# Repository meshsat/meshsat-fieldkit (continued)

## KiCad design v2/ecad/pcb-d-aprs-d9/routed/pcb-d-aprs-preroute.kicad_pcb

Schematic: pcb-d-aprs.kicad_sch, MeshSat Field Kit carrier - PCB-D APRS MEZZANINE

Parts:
C1, C2, C5: 47u 6.3V X5R 1210; C_1210_3225Metric
C3, C9, C17, C24, C25, C33, C40: 10u; C_0805_2012Metric
C4, C6, C11, C15, C16, C39, C49, C50, C51, C52, C53, C54, C55, C56, C57, C62, C63: 100n; C_0603_1608Metric
C7, C8, C12, C18, C19, C20, C21, C22, C23, C28, C29, C30, C31, C32, C34, C35, C36, C37, C38, C41, C42, C46, C47, C48: 1u; C_0603_1608Metric
C10: 4.7u; C_0805_2012Metric
C13, C14: 27p NP0; C_0402_1005Metric
C26, C27: 18p NP0; C_0402_1005Metric
C43: 100p NP0; C_0402_1005Metric
C44, C45: 1n NP0; C_0402_1005Metric
C58, C60: 22p 500V NP0 1206; C_1206_3216Metric
C59: 39p 500V NP0 1206; C_1206_3216Metric
C61: 4.7n; C_0402_1005Metric
D1: SMBJ5.0A; D_SMB
D2: 1N4148W coil flyback; D_SOD-123
FB1: 600R 2A ferrite (the exciter's 1 A transmit pulse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; L_0805_2012Metric
JP1: electret bias headset 1 (close for an electret mi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; SolderJumper-2_P1.3mm_Open_RoundedPad1.0x1.5mm
JP2: electret bias headset 2; SolderJumper-2_P1.3mm_Open_RoundedPad1.0x1.5mm
J_ANT: SMA jack: antenna pigtail to A22's VHF jack J_RF1; SMA_Amphenol_132134_Vertical; LCSC C3174425
J_HARN1: A22 mezzanine harness J_MEZZ1 (IDC 2x8): USB pair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; IDC-Header_2x08_P2.54mm_Vertical_NarrowPad
J_HS1: JST-PH 1x5 socket: headset 1, SPK GND MIC GND PTT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; JST_PH_B5B-PH-K_1x05_P2.00mm_Vertical; LCSC C157993
J_HS2: JST-PH 1x5 socket: headset 2, SPK GND MIC GND PTT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; JST_PH_B5B-PH-K_1x05_P2.00mm_Vertical; LCSC C157993
J_PAIN: U.FL socket: PA drive (coax to the RA30H1317M1 in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; U.FL_Hirose_U.FL-R-SMT-1_Vertical; LCSC C88373
J_PAOUT: SMA jack: PA output (coax from the RA30H1317M1 ou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; SMA_Amphenol_132134_Vertical; LCSC C3174425
J_PWR1: JST-VH socket, 10 A: 5 V from A22 J_MEZZ_PWR1 (be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; JST_VH_B2P-VH_1x02_P3.96mm_Vertical; LCSC C274411
J_USB3: JST-PH 1x4 socket: spare hub port 3, 5V D- D+ GND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; JST_PH_B4B-PH-K_1x04_P2.00mm_Vertical; LCSC C131334
J_VGG: JST-PH 1x2 socket: PA gate bias, VGG GND (the lea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; JST_PH_B2B-PH-K_1x02_P2.00mm_Vertical; LCSC C5251182
K1: Omron G6K-2F-Y 5 VDC DPDT signal relay, T/R; Relay_DPDT_Omron_G6K-2F-Y
L1: 68nH 0805 (LPF, 145 MHz 5th order; values to be v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; L_0805_2012Metric
L2: 68nH 0805 (LPF); L_0805_2012Metric
LED1: green power; LED_0603_1608Metric; LCSC C12624
LED2: amber record; LED_0603_1608Metric; LCSC C2287
LED3: green playback; LED_0603_1608Metric; LCSC C12624
LED4: red transmit; LED_0603_1608Metric; LCSC C2286
LED5: amber PA keyed; LED_0603_1608Metric; LCSC C2287
LED6: green receive (AUDIO_ON low); LED_0603_1608Metric; LCSC C12624
Q1: 2N7002 PA_EN -> H/L low (never tie H/L high); SOT-23; LCSC C8545
Q2: 2N7002 relay coil; SOT-23; LCSC C8545
Q3, Q4, Q5, Q6, Q7, Q8, Q9: 2N7002; SOT-23; LCSC C8545
R1, R43, R44, R51: 2.2k; R_0603_1608Metric
R2, R3, R34, R53: 100k; R_0603_1608Metric
R4, R29, R30, R49, R50, R52: 1k; R_0603_1608Metric
R5, R9, R10, R31, R32, R35, R36, R37, R38, R39, R45, R46, R47, R66, R67, R68, R69, R70, R71, R72, R73, R74, R75, R76, R77, R78, R79: 10k; R_0603_1608Metric
R6, R7, R12, R13, R16, R17, R20, R21: 22; R_0603_1608Metric
R8, R11, R28: 1.5k; R_0603_1608Metric
R14, R15, R18, R19, R22, R23, R24, R25: 15k; R_0603_1608Metric
R26, R27: 33; R_0603_1608Metric
R33, R40, R41: 4.7k; R_0603_1608Metric
R42: 220k; R_0603_1608Metric
R48: 100; R_0603_1608Metric
R54, R56: 27 1% 2010; R_2010_5025Metric
R55: 36 1% 2010; R_2010_5025Metric
TP1: AF_OUT; TestPoint_Pad_D1.5mm
TP2: MIC_SUM; TestPoint_Pad_D1.5mm
TP3: KEY; TestPoint_Pad_D1.5mm
TP4: PA_KEY; TestPoint_Pad_D1.5mm
TP5: +3V3_D8; TestPoint_Pad_D1.5mm
TP6: +5V_D8; TestPoint_Pad_D1.5mm
TP7: VGG_SW; TestPoint_Pad_D1.5mm
TP8: RX_MIX; TestPoint_Pad_D1.5mm
TP9: ZEROIZE_HW; TestPoint_Pad_D1.5mm
TP10: AB_SPARE; TestPoint_Pad_D1.5mm
TP11: SA_TXD; TestPoint_Pad_D1.5mm
TP12: SA_RXD; TestPoint_Pad_D1.5mm
TP13: PTT_SW_n; TestPoint_Pad_D1.5mm
TP14: SA_PD; TestPoint_Pad_D1.5mm
TP15: TX_INHIBIT_n; TestPoint_Pad_D1.5mm
TP16: PA_EN; TestPoint_Pad_D1.5mm
TP17: EXP_SPARE1; TestPoint_Pad_D1.5mm
TP18: EXP_SPARE2; TestPoint_Pad_D1.5mm
TP19: EXP_SPARE3; TestPoint_Pad_D1.5mm
TP20: EXP_SPARE4; TestPoint_Pad_D1.5mm
TP21: EXP_SPARE5; TestPoint_Pad_D1.5mm
TP22: EXP_SPARE6; TestPoint_Pad_D1.5mm
TP23: EXP_SPARE7; TestPoint_Pad_D1.5mm
TP24: EXP_SPARE8; TestPoint_Pad_D1.5mm
U1: TLV75533PDBV 3.3 V 500 mA LDO (1 IN 2 GND 3 EN 4 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; SOT-23-5
U2: NiceRF SA868 VHF 2 W exciter, bench-fitted (caste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; NiceRF_SA868
U3: CP2102N-A02-GQFN28 USB-UART bridge (SAU); QFN-28-1EP_5x5mm_P0.5mm_EP3.35x3.35mm; LCSC C964632
U4: TUSB2046BI four-port USB 2.0 full-speed hub (LQFP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; LQFP-32_7x7mm_P0.8mm
U5: USBLC6-2SC6; SOT-23-6; LCSC C7519
U6: TI PCM2912A USB audio codec (TQFP-32): mono input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; TQFP-32_7x7mm_P0.8mm
U7: TI TPA6132A2 headphone amplifier (QFN-16), receiv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; QFN-16-1EP_3x3mm_P0.5mm_EP1.75x1.75mm
U8: TLV9062IDGK dual op amp (1 OUT1 2 IN1- 3 IN1+ 4 V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; VSSOP-8_3x3mm_P0.65mm
U9: 74LVC1G08 AND (1 A 2 B 3 GND 4 Y 5 VCC): both hea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; SOT-23-5
U10: 74LVC1G08 AND: headsets AND software PTT (RTS); SOT-23-5
U11: 74LVC1G04 inverter (2 A 4 Y): PTT_ANY; SOT-23-5
U12: 74LVC1G08 AND: KEY = PTT_ANY AND TX_INHIBIT_n (th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; SOT-23-5
U13: 74LVC1G04 inverter: KEY -> SA868 PTT (low = trans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; SOT-23-5
U14: 74LVC1G08 AND: PA_KEY = KEY AND PA_EN (A22's PA r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; SOT-23-5
U15: TPS22810DRV; WSON-6-1EP_2x2mm_P0.65mm_EP1x1.6mm
U16: PCA9555PW 0x26: COS, PTT states, KEY, PA_KEY in; 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; TSSOP-24_4.4x7.8mm_P0.65mm
Y1: 6 MHz 3225 (CL 20 pF; C1 = C2 = 27 pF and Rd 1.5k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; Crystal_SMD_3225-4Pin_3.2x2.5mm
Y2: 6 MHz 3225 (codec clock; 18 pF loads, to confirm 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; Crystal_SMD_3225-4Pin_3.2x2.5mm

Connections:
/+3V3: C63.1, J_HARN1.13, R67.2, R69.2, R71.2, R73.2, R75.2, R77.2, R79.2, U16.2 (A1), U16.3 (A2), U16.24 (VDD)
/+3V3_D8: C8.1, C9.1, C15.1, C16.1, C17.1, C51.1, C52.1, C53.1, C54.1, C55.1, C56.1, Q3.1 (G), Q4.1 (G), Q5.1 (G), Q6.1 (G), Q7.1 (G), Q8.1 (G), Q9.1 (G), R1.1, R5.2, R8.2, R9.2, R10.2, R29.1, R30.1, R51.1, R66.2, R68.2, R70.2, R72.2, R74.2, R76.2, R78.2, TP5.1, U1.5 (+3V3_D8), U4.3 (VCC), U4.6 (EEDATA/GANGED), U4.25 (VCC), U4.26 (EXTMEM), U7.6 (G0), U9.5 (+3V3_D8), U10.5 (+3V3_D8), U11.5 (+3V3_D8), U12.5 (+3V3_D8), U13.5 (+3V3_D8), U14.5 (+3V3_D8)
/+5V_D8: C1.1, C2.1, C3.1, C4.1, C7.1, C18.1, C32.1, C33.1, C39.1, C57.1, D1.2 (A2), D2.1 (K), FB1.1, J_PWR1.1, J_USB3.1, K1.1, R38.1, R43.2, R44.2, TP6.1, U1.1 (+5V_D8), U1.3 (+5V_D8), U3.7 (VREGIN), U3.8 (VBUS), U5.5 (VBUS), U6.2 (VBUS), U7.14 (VDD), U8.8 (+5V_D8), U15.6 (VIN)
/+5V_SA: C5.1, C6.1, FB1.2, U2.8 (VBAT)
/AB_SPARE: J_HARN1.16, TP10.1
/AF_DIV: C28.1, R31.2, R32.1
/AF_OUT: R31.1, R35.1, TP1.1, U2.3 (AF_OUT)
/AMP_CPN: C30.2, U7.9 (CPN)
/AMP_CPP: C30.1, U7.11 (CPP)
/AMP_EN: Q9.2 (S), R78.1, U7.13 (EN)
/AMP_HPVDD: C31.1, U7.12 (HPVDD)
/AMP_HPVSS: C29.1, U7.8 (HPVSS)
/AMP_INL_N: C37.1, U7.1 (INL-)
/AMP_INL_P: C35.2, U7.2 (INL+)
/AMP_INR_N: C38.1, U7.4 (INR-)
/AMP_INR_P: C36.2, U7.3 (INR+)
/EXP_INT: J_HARN1.12, U16.1 (~INT)
/EXP_SPARE1: TP17.1, U16.13 (IO1_0)
/EXP_SPARE2: TP18.1, U16.14 (IO1_1)
/EXP_SPARE3: TP19.1, U16.15 (IO1_2)
/EXP_SPARE4: TP20.1, U16.16 (IO1_3)
/EXP_SPARE5: TP21.1, U16.17 (IO1_4)
/EXP_SPARE6: TP22.1, U16.18 (IO1_5)
/EXP_SPARE7: TP23.1, U16.19 (IO1_6)
/EXP_SPARE8: TP24.1, U16.20 (IO1_7)
/HS1_BIAS_R: JP1.2 (B), R43.1
/HS1_MIC: C41.1, C44.1, JP1.1 (A), J_HS1.3
/HS1_MIC_AC: C41.2, R40.1
/HS1_SPK: J_HS1.1, U7.16 (OUTL)
/HS2_BIAS_R: JP2.2 (B), R44.1
/HS2_MIC: C42.1, C45.1, JP2.1 (A), J_HS2.3
/HS2_MIC_AC: C42.2, R41.1
/HS2_SPK: J_HS2.1, U7.5 (OUTR)
/HUB_DM0: R7.2, U4.2 (DM0)
/HUB_DM1: R13.1, U4.11 (DM1)
/HUB_DM2: R17.1, U4.15 (DM2)
/HUB_DM3: R21.1, U4.19 (DM3)
/HUB_DM4: R25.1, U4.23 (DM4)
/HUB_DP0: R6.2, R8.1, U4.1 (DP0)
/HUB_DP1: R12.1, U4.12 (DP1)
/HUB_DP2: R16.1, U4.16 (DP2)
/HUB_DP3: R20.1, U4.20 (DP3)
/HUB_DP4: R24.1, U4.24 (DP4)
/HUB_OVRCUR_n: R9.1, U4.10 (OVRCUR1_n), U4.14 (OVRCUR2_n), U4.18 (OVRCUR3_n), U4.22 (OVRCUR4_n)
/HUB_RST_n: C12.1, R10.1, U4.4 (RESET_n)
/HUB_XTAL1: C13.1, U4.30 (XTAL1), Y1.1
/HUB_XTAL2: R11.2, U4.29 (XTAL2)
/HUB_XTAL2R: C14.1, R11.1, Y1.3
/KEY: Q6.2 (S), R48.1, R49.1, R72.1, TP3.1, U12.4 (KEY), U13.2 (KEY), U14.1 (KEY)
/LED_PA_A: LED5.2 (A), R50.2
/LED_PLAY_A: LED3.2 (A), R30.2
/LED_PLAY_K: LED3.1 (K), U6.32 (PLAY)
/LED_PWR_A: LED1.2 (A), R1.2
/LED_REC_A: LED2.2 (A), R29.2
/LED_REC_K: LED2.1 (K), U6.31 (REC)
/LED_RX_A: LED6.2 (A), R51.2
/LED_TX_A: LED4.2 (A), R49.2
/MICAMP_AC: C46.2, R45.1
/MICAMP_IN_N: C43.2, R40.2, R41.2, R42.2, U8.2 (MICAMP_IN_N)
/MICAMP_OUT: C43.1, C46.1, R42.1, U8.1 (MICAMP_OUT)
/MIC_IN: C48.2, U2.18 (MIC_IN)
/MIC_SUM: C48.1, R45.2, R46.2, R47.1, TP2.1
/MMUTE: R33.2, R34.1, U6.30 (MMUTE)
/OPB_OUT: U8.6 (OPB_OUT), U8.7 (OPB_OUT)
/PA_EN: J_HARN1.9, Q1.1 (G), R3.1, TP16.1, U14.2 (PA_EN)
/PA_KEY: Q7.2 (S), R50.1, R52.1, R74.1, TP4.1, U14.4 (PA_KEY), U15.5 (EN/UVLO)
/PCM_L_AC: C34.2, R36.1
/PCM_R_AC: C47.2, R46.1
/PCM_VCCA: C20.1, U6.15 (VCCA)
/PCM_VCCL: C21.1, U6.19 (VCCL)
/PCM_VCCP: C23.1, U6.26 (VCCP)
/PCM_VCCR: C22.1, U6.21 (VCCR)
/PCM_VCOM1: C24.1, U6.11 (VCOM1)
/PCM_VCOM2: C25.1, U6.12 (VCOM2)
/PCM_VDD: C19.1, R28.2, U6.5 (VDD), U6.27 (TEST1)
/PCM_VIN: C28.2, U6.16 (VIN)
/PCM_VOUTL: C34.1, U6.18 (VOUTL)
/PCM_VOUTR: C47.1, U6.22 (VOUTR)
/PCM_XTI: C26.1, U6.8 (XTI), Y2.1
/PCM_XTO: C27.1, U6.7 (XTO), Y2.3
/PTT_ANY: U11.4 (PTT_ANY), U12.1 (PTT_ANY)
/PTT_ANY_n: U10.4 (PTT_ANY_n), U11.2 (PTT_ANY_n)
/PTT_HS1_n: C49.1, J_HS1.5, Q4.2 (S), R68.1, U9.1 (PTT_HS1_n)
/PTT_HS2_n: C50.1, J_HS2.5, Q5.2 (S), R70.1, U9.2 (PTT_HS2_n)
/PTT_HS_n: U9.4 (PTT_HS_n), U10.1 (PTT_HS_n)
/PTT_SW_n: R5.1, TP13.1, U3.24 (RTS), U10.2 (PTT_SW_n)
/RF_ANT: J_ANT.1 (In), K1.6
/RF_DRV: J_PAIN.1 (In), R56.2
/RF_LPF_M: C59.1, L1.2, L2.1
/RF_LPF_OUT: C60.1, K1.5, L2.2
/RF_PAD_IN: K1.4, R54.1
/RF_PAD_M: R54.2, R55.1, R56.1
/RF_PAOUT: C58.1, J_PAOUT.1 (In), L1.1
/RF_RX: K1.2, K1.7
/RF_SA: K1.3, U2.12 (ANT)
/RLY_DRV: Q2.1 (G), R52.2, R53.1
/RLY_K: D2.2 (A), K1.8, Q2.3 (D)
/RX_MIX: C35.1, C36.1, R35.2, R36.2, R37.1, TP8.1
/SAU_3V3: C10.1, C11.1, R4.2, U3.6 (VDD)
/SAU_RST: R4.1, U3.9 (RSTb)
/SA_AUDIO_ON_n: LED6.1 (K), Q3.2 (S), R66.1, U2.1 (AUDIO_ON_n)
/SA_HL: Q1.3 (D), U2.7 (H/L)
/SA_PD: Q8.2 (S), R76.1, TP14.1, U2.6 (PD)
/SA_PTT_n: U2.5 (PTT_n), U13.4 (SA_PTT_n)
/SA_RXD: TP12.1, U2.16 (RXD), U3.26 (TXD)
/SA_TXD: TP11.1, U2.17 (TXD), U3.25 (RXD)
/SCL: J_HARN1.11, U16.22 (SCL)
/SDA: J_HARN1.10, U16.23 (SDA)
/TR_APRS: J_HARN1.7, R48.2
/TX_INHIBIT_n: J_HARN1.8, R2.1, TP15.1, U12.2 (TX_INHIBIT_n)
/USB1_N: R13.2, R15.1, R27.1
/USB1_NR: R27.2, U6.3 (D-)
/USB1_P: R12.2, R14.1, R26.1
/USB1_PR: R26.2, R28.1, U6.4 (D+)
/USB2_N: R17.2, R19.1, U3.5 (D-)
/USB2_P: R16.2, R18.1, U3.4 (D+)
/USB3_N: J_USB3.2, R21.2, R23.1
/USB3_P: J_USB3.3, R20.2, R22.1
/USB_D8_N: J_HARN1.2, R7.1, U5.3 (I/O2), U5.4 (I/O2)
/USB_D8_P: J_HARN1.1, R6.1, U5.1 (I/O1), U5.6 (I/O1)
/VGG_CT: C61.1, U15.3 (CT)
/VGG_SW: C62.1, J_VGG.1, TP7.1, U15.1 (VOUT)
/VREF: C40.1, R38.2, R39.1, U8.3 (VREF), U8.5 (VREF)
/X_AMP_EN: Q9.3 (D), R79.1, U16.10 (IO0_6)
/X_COS_n: Q3.3 (D), R67.1, U16.4 (IO0_0)
/X_KEY: Q6.3 (D), R73.1, U16.7 (IO0_3)
/X_MMUTE: R33.1, U16.11 (IO0_7)
/X_PA_KEY: Q7.3 (D), R75.1, U16.8 (IO0_4)
/X_PTT_HS1_n: Q4.3 (D), R69.1, U16.5 (IO0_1)
/X_PTT_HS2_n: Q5.3 (D), R71.1, U16.6 (IO0_2)
/X_SA_PD: Q8.3 (D), R77.1, U16.9 (IO0_5)
/ZEROIZE_HW: J_HARN1.15, TP9.1
GND: C1.2, C2.2, C3.2, C4.2, C5.2, C6.2, C7.2, C8.2, C9.2, C10.2, C11.2, C12.2, C13.2, C14.2, C15.2, C16.2, C17.2, C18.2, C19.2, C20.2, C21.2, C22.2, C23.2, C24.2, C25.2, C26.2, C27.2, C29.2, C31.2, C32.2, C33.2, C37.2, C38.2, C39.2, C40.2, C44.2, C45.2, C49.2, C50.2, C51.2, C52.2, C53.2, C54.2, C55.2, C56.2, C57.2, C58.2, C59.2, C60.2, C61.2, C62.2, C63.2, D1.1 (A1), J_ANT.2 (Ext), J_HARN1.3, J_HARN1.4, J_HARN1.5, J_HARN1.6, J_HARN1.14, J_HS1.2, J_HS1.4, J_HS2.2, J_HS2.4, J_PAIN.2 (Ext), J_PAOUT.2 (Ext), J_PWR1.2, J_USB3.4, J_VGG.2, LED1.1 (K), LED4.1 (K), LED5.1 (K), Q1.2 (S), Q2.2 (S), R2.2, R3.2, R14.2, R15.2, R18.2, R19.2, R22.2, R23.2, R24.2, R25.2, R32.2, R34.2, R37.2, R39.2, R47.2, R53.2, R55.2, U1.2 (GND), U2.9 (GND), U2.10 (GND), U3.3 (GND), U3.29 (GND), U4.7 (GND), U4.8 (BUSPWR), U4.27 (TSTPLL/48MCLK), U4.28 (GND), U4.31 (TSTMODE), U5.2 (GND), U6.1 (BGND), U6.6 (DGND), U6.13 (AGND), U6.20 (HGND), U6.23 (MAMP), U6.24 (POWER), U6.25 (PGND), U6.28 (TEST0), U7.7 (G1), U7.10 (PGND), U7.15 (SGND), U7.17 (PAD), U8.4 (GND), U9.3 (GND), U10.3 (GND), U11.3 (GND), U12.3 (GND), U13.3 (GND), U14.3 (GND), U15.4 (GND), U15.7 (GND), U16.12 (VSS), U16.21 (A0), Y1.2 (G), Y1.4 (G), Y2.2 (G), Y2.4 (G)

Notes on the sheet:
PCB-D APRS MEZZANINE D12
HARNESS, 5 V ENTRY, 3.3 V LDO, EXCITER SUPPLY | SA868 EXCITER, UART BRIDGE, T/R RELAY, 10 dB PAD, LPF, PA LEADS, GATE BIAS SWITCH
HARNESS, 5 V ENTRY, 3.3 V LDO, EXCITER SUPPLY
SA868 EXCITER, UART BRIDGE, T/R RELAY, 10 dB PAD, LPF, PA LEADS, GATE BIAS SWITCH
page 1 of 5 MeshSat field kit V2, CERN-OHL-S-2.0 PROTOTYPE, nothing built 2026-09-17
A22 mezzanine harness J_MEZZ1
JST-VH socket
47u 6.3V
600R 2A
TLV75533PDBV 3.3 V 500 mA LDO
NiceRF SA868 VHF 2 W exciter
2N7002 PA_EN -> H/L low
CP2102N-A02-GQFN28 USB-UART bridge
Omron G6K-2F-Y 5 VDC DPDT signal r..
27 1%
68nH 0805
U.FL socket
SMA jack
22p 500V
39p 500V
p4,5
p3,5
SA868 EXCITER, UART BRIDGE, T/R RELAY, 10 dB PAD, LPF, PA LEADS, GATE BIAS SWITCH | USB HUB TUSB2046B, PORT TERMINATIONS, SPARE PORT
SA868 EXCITER, UART BRIDGE, T/R RELAY, 10 dB PAD, LPF, PA LEADS, GATE BIAS SWITCH (continued)
USB HUB TUSB2046B, PORT TERMINATIONS, SPARE PORT
page 2 of 5 MeshSat field kit V2, CERN-OHL-S-2.0 PROTOTYPE, nothing built 2026-09-17
JST-PH 1x2 socket
TUSB2046BI four-port USB 2.0 full-..
6 MHz 3225
JST-PH 1x4 socket
USB AUDIO CODEC PCM2912A, HEADPHONE AMPLIFIER, MIC PREAMP, HEADSET LEADS
page 3 of 5 MeshSat field kit V2, CERN-OHL-S-2.0 PROTOTYPE, nothing built 2026-09-17
TI PCM2912A USB audio codec
decoupling of U6
TI TPA6132A2 headphone amplifier
TLV9062IDGK dual op amp
p1,5
USB AUDIO CODEC PCM2912A, HEADPHONE AMPLIFIER, MIC PREAMP, HEADSET LEADS | PTT AND EMCON LOGIC, PTT MIRROR, LEDS, EXPANDER 0x26 WITH LEVEL STAGES, TEST POINTS, FLAGS
USB AUDIO CODEC PCM2912A, HEADPHONE AMPLIFIER, MIC PREAMP, HEADSET LEADS (continued)
PTT AND EMCON LOGIC, PTT MIRROR, LEDS, EXPANDER 0x26 WITH LEVEL STAGES, TEST POINTS, FLAGS

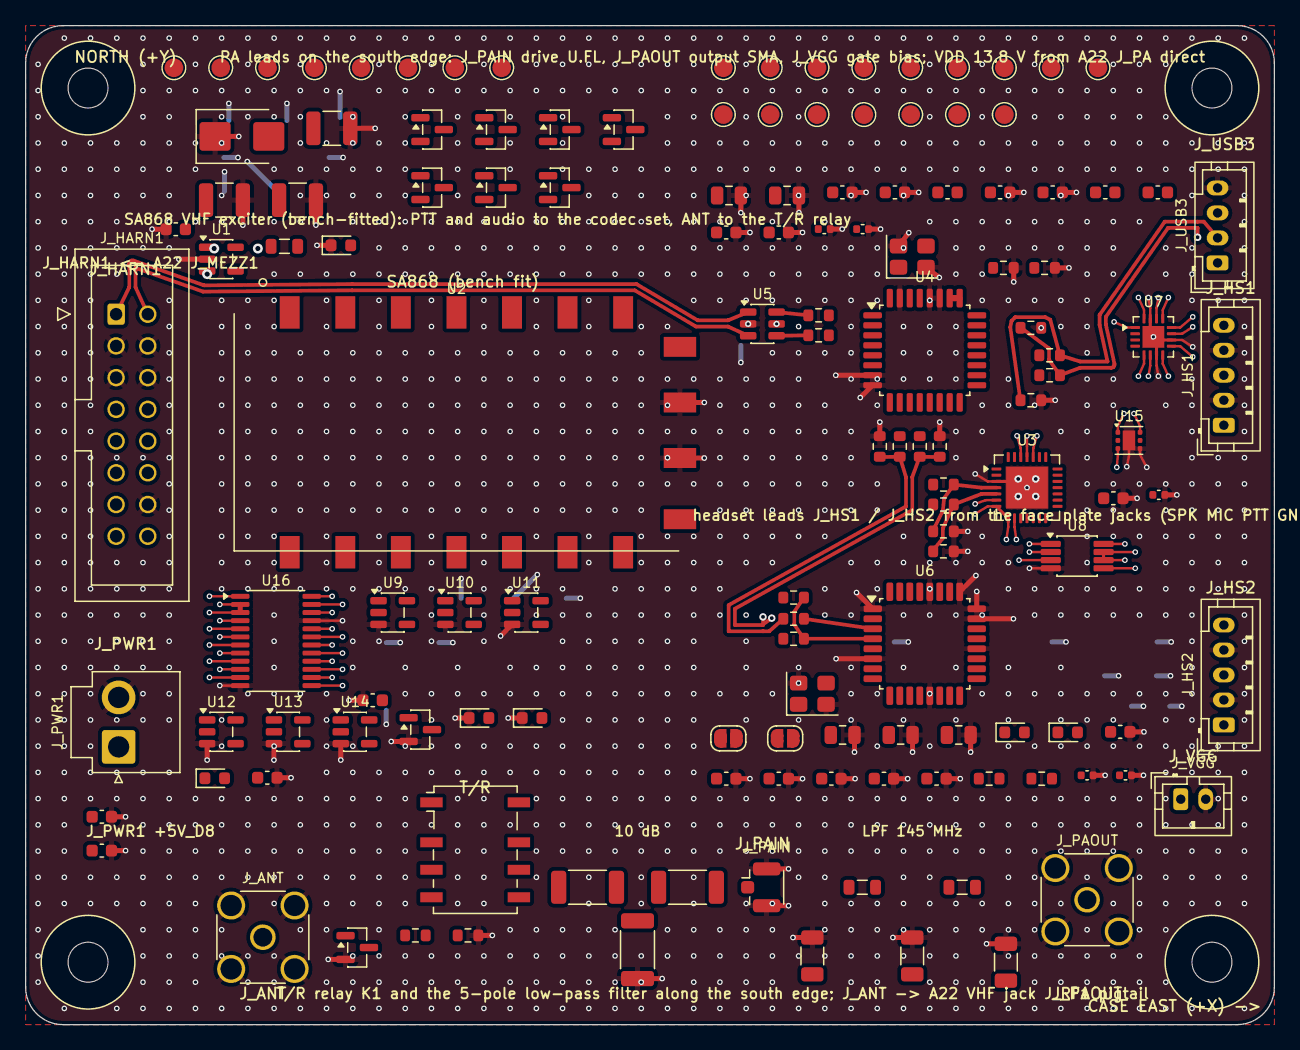
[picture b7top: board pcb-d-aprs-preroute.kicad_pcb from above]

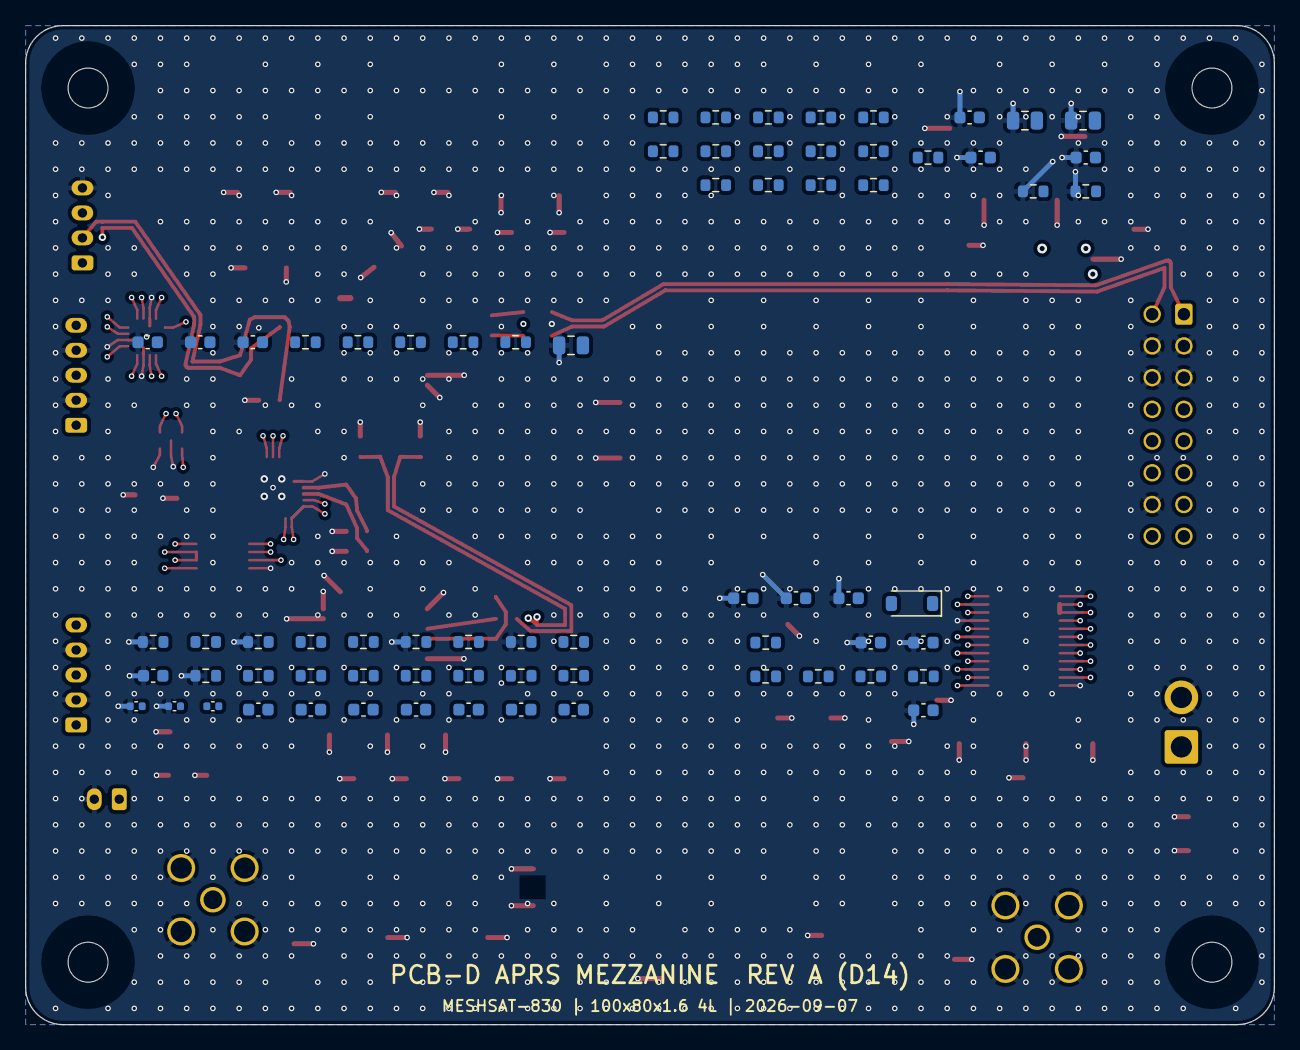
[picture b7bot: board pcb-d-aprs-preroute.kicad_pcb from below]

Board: 4 copper layers, 100.0 x 80.0 mm, 211 parts (71 on the bottom side), 133 nets.

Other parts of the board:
H1, H2, H3, H4: M3 standoff on A22 (5/95, +-35); MountingHole_3.2mm_M3

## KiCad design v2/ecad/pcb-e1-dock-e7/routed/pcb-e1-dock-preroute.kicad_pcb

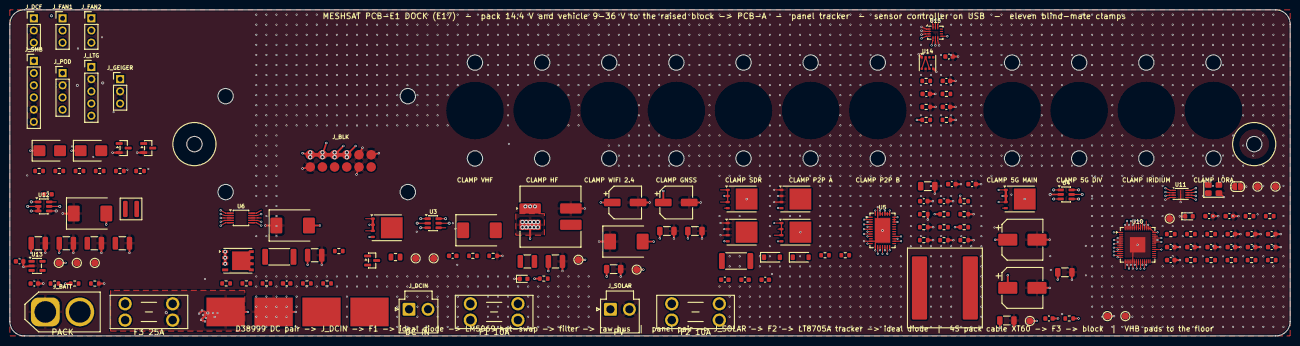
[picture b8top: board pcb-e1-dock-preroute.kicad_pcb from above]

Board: 4 copper layers, 267.0 x 68.0 mm, 189 parts (0 on the bottom side), 94 nets.

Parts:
C1, C31: 10u 25V 1210; C_1210_3225Metric
C2: 100n 100V; C_0805_2012Metric
C4, C28: 100n 50V; C_0603_1608Metric
C5: 100n (TIMER); C_0603_1608Metric
C6: 1u 100V 1210 (X, input side); C_1210_3225Metric
C7: 1u 100V 1210 (X, bus side); C_1210_3225Metric
C8: 10u 100V X7R 1210; C_1210_3225Metric
C11, C12: 100u 35V Panasonic EEHZK1V101XP hybrid polymer (7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; CP_Elec_6.3x7.7
C13, C14: 10u 50V; C_1206_3216Metric
C15: 4.7u 50V; C_1206_3216Metric
C16: 1n; C_0603_1608Metric
C17, C18: 470n 25V; C_0603_1608Metric
C19: 4.7u 25V; C_1206_3216Metric
C20, C34, C35, C45, C46, C47: 1u; C_0603_1608Metric
C21: 4.7n; C_0603_1608Metric
C22: 100p; C_0603_1608Metric
C23, C30, C38, C39, C40, C41, C42, C43, C44, C48, C49, C50, C51: 100n; C_0603_1608Metric
C24, C25: 39u 35V Panasonic 35SVPF39M polymer (6.9 mm); CP_Elec_8x6.7
C26, C27: 10u 25V; C_1206_3216Metric
C32, C33: 22u 10V X7R 1210; C_1210_3225Metric
C36, C37: 15p; C_0603_1608Metric
D1: SMCJ40A (input surge: 40 V standoff on a line spe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; D_SMC
D2: SMCJ40A (bus clamp: 40 V standoff on the 9 to 36 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; D_SMC
D3: SMCJ18A (pack node clamp); D_SMC
D4: SMCJ28A (panel surge: 28 V standoff, conducting f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; D_SMC
D5: BAT54 boost diode INTVCC -> BOOST1; D_SOD-123
D6: BAT54 boost diode INTVCC -> BOOST2; D_SOD-123
D7: SS14 flyback across fan 1; D_SMB
D8: SS14 flyback across fan 2; D_SMB
F1: 10 A mini blade (Keystone 3568 holder): vehicle i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; Fuseholder_Blade_Mini_Keystone_3568
F2: 10 A mini blade (Keystone 3568 holder): panel inp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; Fuseholder_Blade_Mini_Keystone_3568
F3: 25 A mini blade (Keystone 3568 holder): pack to t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; Fuseholder_Blade_Mini_Keystone_3568
H1, H2: M3 rod pass-through, PCB-A standoff stands here; MountingHole_3.2mm_M3
H3, H4, H5, H6: M3 standoff, raised block; MountingHole_3.2mm_M3
H7, H8: M3, float clamp VHF; MountingHole_3.2mm_M3
H9, H10: M3, float clamp HF; MountingHole_3.2mm_M3
H11, H12: M3, float clamp WIFI 2.4; MountingHole_3.2mm_M3
H13, H14: M3, float clamp GNSS; MountingHole_3.2mm_M3
H15, H16: M3, float clamp SDR; MountingHole_3.2mm_M3
H17, H18: M3, float clamp P2P A; MountingHole_3.2mm_M3
H19, H20: M3, float clamp P2P B; MountingHole_3.2mm_M3
H21, H22: M3, float clamp 5G MAIN; MountingHole_3.2mm_M3
H23, H24: M3, float clamp 5G DIV; MountingHole_3.2mm_M3
H25, H26: M3, float clamp IRIDIUM; MountingHole_3.2mm_M3
H27, H28: M3, float clamp LORA; MountingHole_3.2mm_M3
JP1: BOOTSEL: short while powering to enter the USB bo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; SolderJumper-2_P1.3mm_Open_RoundedPad1.0x1.5mm
J_BATT: Amass XT60-M: the BB-2590/U pack cable BTA-70762-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; AMASS_XT60-M_1x02_P7.20mm_Vertical
J_BLK: solder lands for the 12 signal wires to the block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; PogoTargets_2x6
J_DCF: DCF77 receiver module: 3.3 V, GND, pulse; PinHeader_1x03_P2.54mm_Vertical
J_DCIN: JST-VH socket, 10 A: vehicle and shore DC in 9 to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; JST_VH_B2P-VH_1x02_P3.96mm_Vertical
J_FAN1: mixer fan 1 under the plate (12 V class fan on th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; PinHeader_1x03_P2.54mm_Vertical
J_FAN2: mixer fan 2 under the plate (12 V class fan on th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; PinHeader_1x03_P2.54mm_Vertical
J_GEIGER: Geiger counter module (RadiationD-v1.1 class): 5 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; PinHeader_1x03_P2.54mm_Vertical
J_LTG: AS3935 lightning sensor module (CJMCU-3935 class)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; PinHeader_1x05_P2.54mm_Vertical
J_POD: outside sensor pod on the connector plate (M8 sea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; PinHeader_1x04_P2.54mm_Vertical
J_SMB: pack SMBus (XH or pin header): section A SDA SCL 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; PinHeader_1x06_P2.54mm_Vertical
J_SOLAR: JST-VH socket, 10 A: bare panel in (lead from the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; JST_VH_B2P-VH_1x02_P3.96mm_Vertical
L1: 10uH Coilcraft XAL1510-103MED (Isat 26 A, 10.0 mm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; L_Coilcraft_XAL1510-103
L2: Bourns SRF1260-4R7Y dual-winding choke (7.2 A per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; L_CommonModeChoke_Bourns_SRF1260
L3: 4.7uH XAL4030-472ME; L_Coilcraft_XAL4020-XXX
LED1: green: vehicle input present; LED_0603_1608Metric
LED2: status (GPIO25); LED_0603_1608Metric
PAD_W1: water electrode A (bare copper, +3.3 V through 1 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; SolderPad_8x6
PAD_W2: water electrode B (bare copper, to ADC0); SolderPad_8x6
P_CN: solder pad, 12 AWG wire to the block board return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; SolderPad_8x6
P_CP: solder pad, 12 AWG wire to the block board CELL+ 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; SolderPad_8x6
Q1, Q2: BSC039N06NS 60 V 3.9 mOhm N-FET (PG-TDSON-8: 1-3 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; TDSON-8-1
Q3: BSC028N06NS 60 V 2.8 mOhm N-FET, M1 buck top (TDS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; TDSON-8-1
Q4: BSC039N06NS 60 V N-FET, M2 buck bottom; TDSON-8-1
Q5: BSC028N06NS 60 V N-FET, M3 boost bottom; TDSON-8-1
Q6: BSC039N06NS 60 V N-FET, M4 boost top; TDSON-8-1
Q7: CSD19532Q5B 100 V N-FET (4.6 mOhm at VGS 6 V, Pow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; PowerPAK_SO-8_Single
Q8: 2N7002: SHORE_INHIBIT high pulls UVLO low = input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; SOT-23
Q9: 2N7002 fan 1 low-side switch (1 G, 2 S, 3 D); SOT-23
Q10: 2N7002 fan 2 low-side switch (1 G, 2 S, 3 D); SOT-23
R1, R18, R26: 100k; R_0603_1608Metric
R5: 5 mOhm 1% 3 W 2512 RSENSE (RALEC LR2512-23R005F4); R_2512_6332Metric
R6, R7, R44, R45: 100R; R_0603_1608Metric
R8: 102k 1% (RFBIN1: panel point 17.6 V); R_0603_1608Metric
R9: 7.50k 1% (RFBIN2); R_0603_1608Metric
R10: 115k 1% (RFBOUT1: 15.1 V); R_0603_1608Metric
R11: 10.0k 1% (RFBOUT2); R_0603_1608Metric
R12: 215k 1% (RT: 202 kHz); R_0603_1608Metric
R13, R16, R17, R25, R31, R46, R47, R49, R50: 10k; R_0603_1608Metric
R14, R20, R22, R40, R42: 100k 1%; R_0603_1608Metric
R15: 15.0k 1% (SHDN: enable above about 9.5 V); R_0603_1608Metric
R19: 10mOhm 1% 2512 (hot-swap sense); R_2512_6332Metric
R21: 38.3k 1% (UVLO: 9 V); R_0603_1608Metric
R23: 6.65k 1% (OVLO: 40 V); R_0603_1608Metric
R24: 20k (PWR: power limit); R_0603_1608Metric
R27: 2.2k; R_0603_1608Metric
R28, R33: 1k; R_0603_1608Metric
R29, R30: 27R; R_0603_1608Metric
R32: 1k (BOOTSEL); R_0603_1608Metric
R34, R35, R36, R37: 4.7k; R_0603_1608Metric
R38, R39: 1M; R_0603_1608Metric
R41: 10k 1% (ADC1: 0.091 x bus); R_0603_1608Metric
R43: 22k 1% (ADC2: 0.18 x pack); R_0603_1608Metric
R48: 22R (pulse input series); R_0603_1608Metric
R51: 0R (CSB high: I2C mode; its own net keeps the pin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; R_0603_1608Metric
TP1: DC_IN; TestPoint_Pad_D1.5mm
TP2: DC_P; TestPoint_Pad_D1.5mm
TP3: VIN_RAW; TestPoint_Pad_D1.5mm
TP4: GND; TestPoint_Pad_D1.5mm
TP5: PV_P; TestPoint_Pad_D1.5mm
TP6: TRK_OUT; TestPoint_Pad_D1.5mm
TP7: BLK_SPARE; TestPoint_Pad_D1.5mm
TP8: CELL_F; TestPoint_Pad_D1.5mm
TP9: +5V_E6; TestPoint_Pad_D1.5mm
TP10: SWCLK; TestPoint_Pad_D1.5mm
TP11: SWDIO; TestPoint_Pad_D1.5mm
TP12: E6_RUN; TestPoint_Pad_D1.5mm
TP13: GEIGER_IN; TestPoint_Pad_D1.5mm
U3, U4: LM74700-Q1 ideal-diode controller: 1 VCAP 2 GND 3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; SOT-23-6
U5: LT8705A buck-boost controller, 38-lead QFN 5x7 (p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; WQFN-38-1EP_5x7mm_P0.5mm_EP3.15x5.15mm
U6: LM5069MM-2 hot-swap controller: 9 V on, 40 V off,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; VSSOP-10_3x3mm_P0.5mm
U10: RP2040 sensor controller (USB to B16 through the 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; QFN-56-1EP_7x7mm_P0.4mm_EP3.2x3.2mm
U11: W25Q16JVUXIQ 16 Mbit QSPI flash (USON-8: 1 CS 2 D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; Winbond_USON-8-1EP_3x2mm_P0.5mm_EP0.2x1.6mm
U12: AP63205WU-7 5 V 2 A buck for the controller, the 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; TSOT-23-6
U13: TLV75533PDBVR 3.3 V LDO; SOT-23-5
U14: BME688 inside climate: temperature, humidity, pre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; Bosch_LGA-8_3x3mm_P0.8mm_ClockwisePinNumbering
U15: BMI270 six-axis IMU (I2C 0x68): shock and tilt lo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; Bosch_LGA-14_3x2.5mm_P0.5mm
Y1: 12 MHz ABM8-272-T3 (3225): 1 XIN, 3 XOUT, 2 and 4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; Crystal_SMD_3225-4Pin_3.2x2.5mm

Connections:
/+3V3_E6: C35.1, C38.1, C39.1, C40.1, C41.1, C42.1, C43.1, C44.1, C47.1, C48.1, C49.1, C50.1, J_DCF.1, J_LTG.1, J_POD.1, R25.2, R31.2, R34.2, R35.2, R36.2, R37.2, R38.1, R46.2, R47.2, R49.2, R50.2, R51.1, U10.1, U10.10, U10.22, U10.33, U10.42, U10.43, U10.44, U10.48, U10.49, U11.8, U13.5, U14.2, U14.6, U14.8, U15.5, U15.8
/+5V_E6: C32.1, C33.1, C34.1, J_GEIGER.1, L3.2, TP9.1, U12.1, U13.1, U13.3
/BLK_SPARE: J_BLK.12, TP7.1
/BOOT_J: JP1.1, R32.2
/CELL+: F3.1, J_BATT.2
/CELL_F: C1.1, C31.1, D3.2, D7.1, D8.1, F3.2, J_FAN1.1, J_FAN2.1, P_CP.1, R42.1, TP8.1, U12.2, U12.3
/CELL_MON: R42.2, R43.1, U10.40
/DCF_PULSE: J_DCF.3, R49.1, U10.8
/DCIN_PGD: R25.1, U6.8, U10.15
/DC_F: C4.2, F1.2, Q1.1, Q1.2, Q1.3, R1.2, U3.3, U3.6
/DC_HS: C6.1, L2.1, Q7.1, Q7.2, Q7.3, U6.9
/DC_IN: F1.1, J_DCIN.1, TP1.1
/DC_P: C2.1, D1.2, Q1.5, R19.1, R20.1, R22.1, TP2.1, U3.4, U6.2
/E6_BST: C30.1, U12.6
/E6_DVDD: C45.1, C46.1, U10.23, U10.45, U10.50
/E6_RUN: R31.1, TP12.1, U10.26
/E6_SW: C30.2, L3.1, U12.5
/FAN1_G: Q9.1, R44.2
/FAN1_PWM: R44.1, U10.11
/FAN1_SW: D7.2, J_FAN1.2, Q9.3
/FAN1_TACH: J_FAN1.3, R46.1, U10.13
/FAN2_G: Q10.1, R45.2
/FAN2_PWM: R45.1, U10.12
/FAN2_SW: D8.2, J_FAN2.2, Q10.3
/FAN2_TACH: J_FAN2.3, R47.1, U10.14
/GEIGER_IN: R48.2, TP13.1, U10.9
/GEIGER_PULSE: J_GEIGER.3, R48.1
/GND_V: C2.2, C5.2, C6.2, D1.1, J_DCIN.2, L2.3, Q8.2, R21.2, R23.2, R24.2, U3.2, U6.5
/HS_GATE: Q7.4, U6.10
/HS_OVLO: R22.2, R23.1, U6.4
/HS_PWR: R24.1, U6.7
/HS_S: Q7.5, R19.2, U6.1
/HS_TIMER: C5.1, U6.6
/HS_UVLO: Q8.3, R20.2, R21.1, U6.3
/IMU_CSB: R51.2, U15.12
/IMU_INT1: U10.16, U15.4
/LED_A: LED1.2, R27.2
/LED_STAT: R33.1, U10.37
/LED_STAT_A: LED2.2, R33.2
/LTG_IRQ: J_LTG.5, R50.1, U10.17
/PV_IN: F2.1, J_SOLAR.1
/PV_P: C11.1, C12.1, C13.1, C14.1, C15.1, D4.2, F2.2, Q3.5, R8.1, R14.1, TP5.1, U5.32, U5.33, U5.34
/Q1_G: Q1.4, R1.1, U3.5
/Q2_G: Q2.4, R18.1, U4.5
/QSPI_D0: U10.53, U11.5
/QSPI_D1: U10.55, U11.2
/QSPI_D2: U10.54, U11.3
/QSPI_D3: U10.51, U11.7
/QSPI_SCLK: U10.52, U11.6
/QSPI_SS: R32.1, U10.56, U11.1
/SCL0: J_SMB.2, R35.1, U10.5
/SCL1: J_LTG.4, J_POD.4, J_SMB.4, R37.1, U10.7, U14.4, U15.13
/SDA0: J_SMB.1, R34.1, U10.4
/SDA1: J_LTG.3, J_POD.3, J_SMB.3, R36.1, U10.6, U14.3, U15.14
/SHORE_INHIBIT: J_BLK.8, Q8.1, R26.1, U10.18
/SWCLK: TP10.1, U10.24
/SWDIO: TP11.1, U10.25
/TRK_BG1: Q4.4, U5.14
/TRK_BG2: Q5.4, U5.16
/TRK_BOOST1: C17.1, D5.1, U5.23
/TRK_BOOST2: C18.1, D6.1, U5.17
/TRK_CSN: C16.2, R7.2, U5.2
/TRK_CSP: C16.1, R6.2, U5.3
/TRK_FBIN: R8.2, R9.1, U5.5
/TRK_FBOUT: R10.2, R11.1, U5.6
/TRK_IMONI: R16.1, U5.38
/TRK_IMONO: R17.1, U5.7
/TRK_INTVCC: C19.1, D5.2, D6.2, U5.15, U5.35, U5.36
/TRK_LDO33: C20.1, U5.4
/TRK_LSENSE: L1.2, R5.1, R6.1
/TRK_OUT: C24.1, C25.1, C26.1, C27.1, C28.2, Q2.1, Q2.2, Q2.3, Q6.5, R10.1, R18.2, TP6.1, U4.3, U4.6, U5.29, U5.30, U5.31
/TRK_RT: R12.1, U5.12
/TRK_SHDN: R14.2, R15.1, U5.1
/TRK_SS: C23.1, U5.9
/TRK_SW1: C17.2, L1.1, Q3.1, Q3.2, Q3.3, Q4.5, U5.21
/TRK_SW2: C18.2, Q5.5, Q6.1, Q6.2, Q6.3, R5.2, R7.1, U5.19
/TRK_TG1: Q3.4, U5.22
/TRK_TG2: Q6.4, U5.18
/TRK_VC: C22.1, R13.1, U5.8
/TRK_VCC1: C21.1, R13.2
/U3_VCAP: C4.1, U3.1
/U4_VCAP: C28.1, U4.1
/USB_DM_R: R30.1, U10.46
/USB_DP_R: R29.1, U10.47
/USB_E6_N: J_BLK.10, R30.2
/USB_E6_P: J_BLK.9, R29.2
/VIN_MON: R40.2, R41.1, U10.39
/VIN_RAW: C7.1, C8.1, D2.2, J_BLK.1, J_BLK.2, J_BLK.3, J_BLK.4, L2.2, Q2.5, R27.1, R40.1, TP3.1, U4.4
/WATER_A: PAD_W1.1, R38.2
/WATER_SENSE: C51.1, PAD_W2.1, R39.1, U10.38
/XIN: C36.1, U10.20, Y1.1
/XOUT: C37.1, R28.2, Y1.3
/XOUT_R: R28.1, U10.21
GND: C1.2, C7.2, C8.2, C11.2, C12.2, C13.2, C14.2, C15.2, C19.2, C20.2, C21.2, C22.2, C23.2, C24.2, C25.2, C26.2, C27.2, C31.2, C32.2, C33.2, C34.2, C35.2, C36.2, C37.2, C38.2, C39.2, C40.2, C41.2, C42.2, C43.2, C44.2, C45.2, C46.2, C47.2, C48.2, C49.2, C50.2, C51.2, D2.1, D3.1, D4.1, JP1.2, J_BATT.1, J_BLK.5, J_BLK.6, J_BLK.7, J_BLK.11, J_DCF.2, J_GEIGER.2, J_LTG.2, J_POD.2, J_SMB.5, J_SMB.6, J_SOLAR.2, L2.4, LED1.1, LED2.1, P_CN.1, Q4.1, Q4.2, Q4.3, Q5.1, Q5.2, Q5.3, Q9.2, Q10.2, R9.2, R11.2, R12.2, R15.2, R16.2, R17.2, R26.2, R39.2, R41.2, R43.2, TP4.1, U4.2, U5.11, U5.13, U5.37, U5.39, U10.19, U10.57, U11.4, U11.9, U12.4, U13.2, U14.1, U14.5, U14.7, U15.1, U15.2, U15.3, U15.6, U15.7, Y1.2, Y1.4
